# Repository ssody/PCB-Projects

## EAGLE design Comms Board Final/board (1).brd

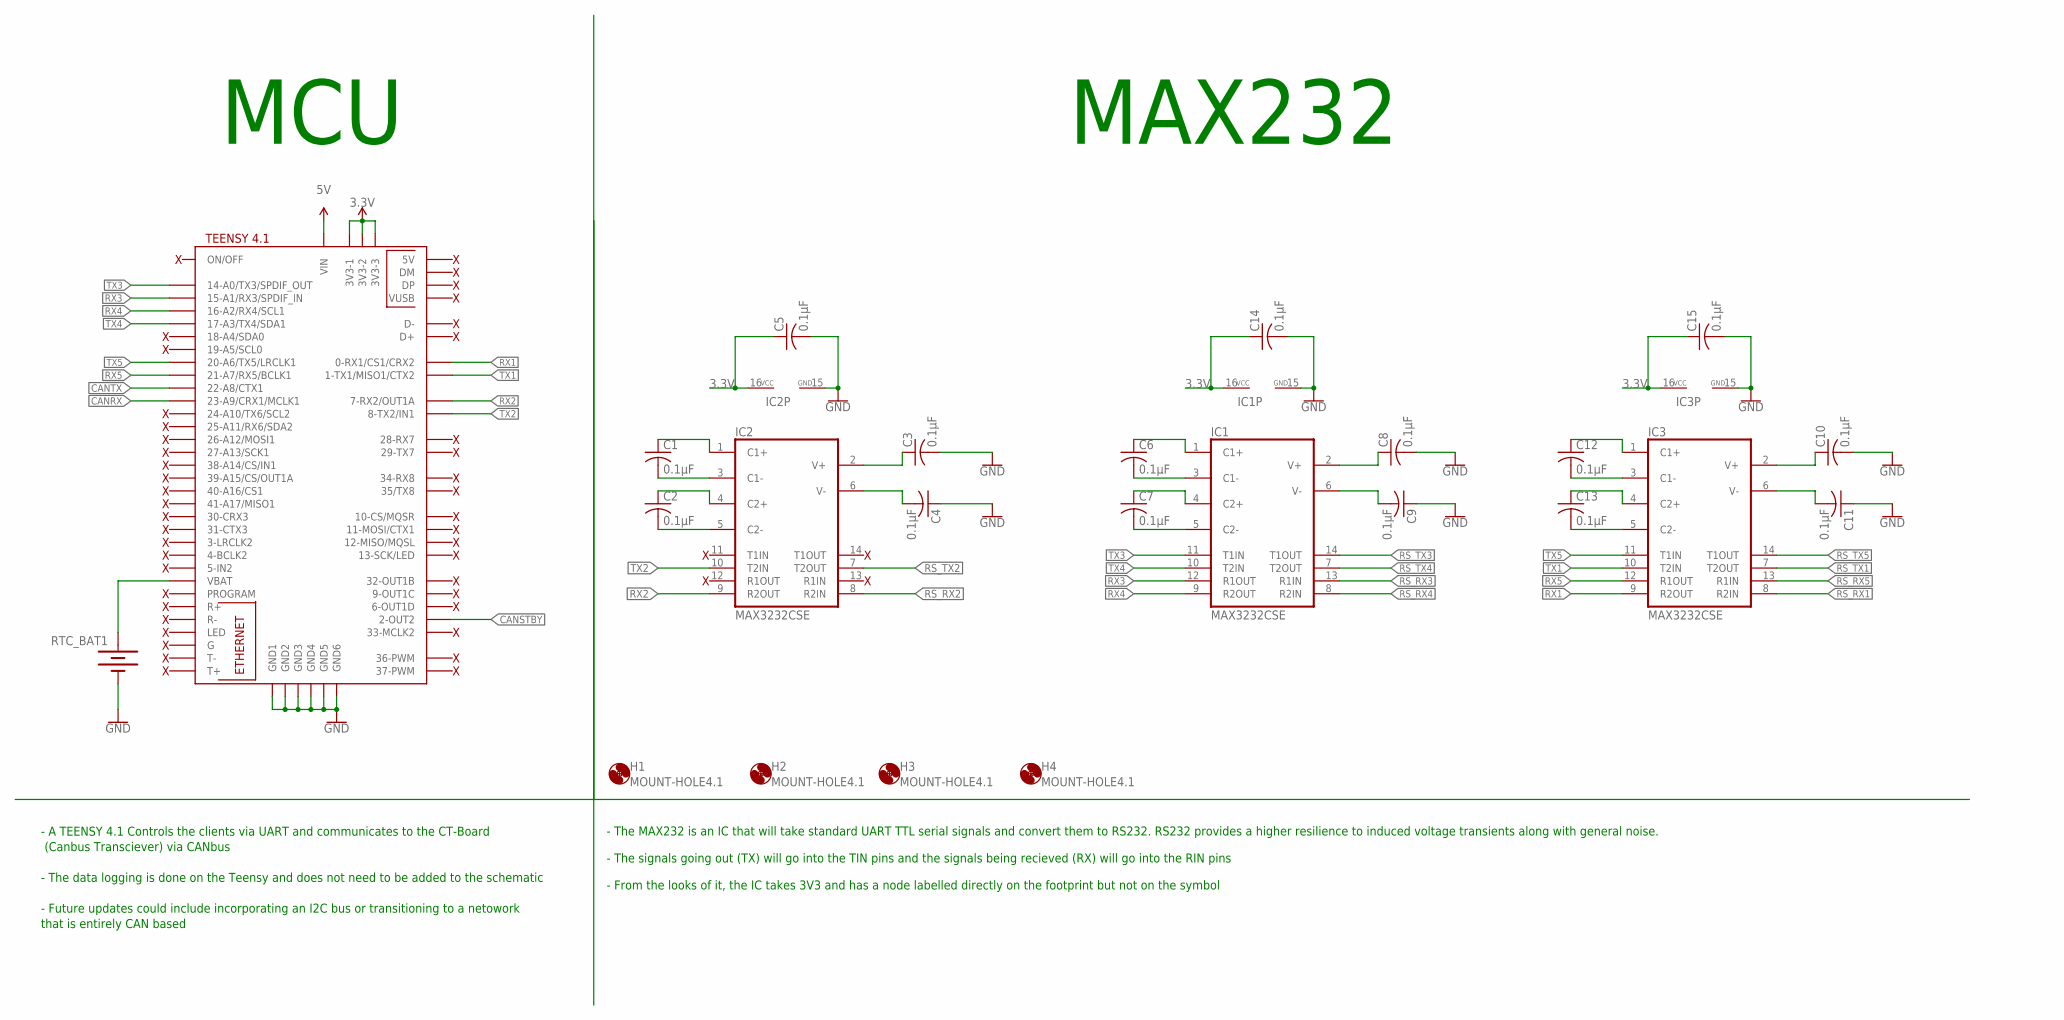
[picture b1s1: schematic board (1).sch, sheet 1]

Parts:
C1, C2, C3, C4, C5, C6, C7, C8, C9, C10, C11, C12, C13, C14, C15: 0.1µF; C0805
H1, H2, H3, H4: MOUNT-HOLE4.1; 4,1
IC1, IC2, IC3: MAX3232CSE; SO16
RTC_BAT1: BATTERY-20MM_PTH; BATTCOM_20MM_PTH
U$1: TEENSY41

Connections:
3.3V: C5.1, C14.1, C15.1, IC1.16 (VCC), IC2.16 (VCC), IC3.16 (VCC), U$1.3V3-1, U$1.3V3-2, U$1.3V3-3; also elsewhere on the board
CANRX: U$1.23-A9/CRX1/MCLK1; also elsewhere on the board
CANSTBY: U$1.2-OUT2; also elsewhere on the board
CANTX: U$1.22-A8/CTX1; also elsewhere on the board
GND: C3.2, C4.1, C5.2, C8.2, C9.1, C10.2, C11.1, C14.2, C15.2, IC1.15 (GND), IC2.15 (GND), IC3.15 (GND), RTC_BAT1.2 (-), U$1.GND1, U$1.GND2, U$1.GND3, U$1.GND4, U$1.GND5, U$1.GND6; also elsewhere on the board
unnamed: C1.1, IC2.1 (C1+)
unnamed: C1.2, IC2.3 (C1-)
unnamed: C2.1, IC2.4 (C2+)
unnamed: C2.2, IC2.5 (C2-)
unnamed: C3.1, IC2.2 (V+)
unnamed: C4.2, IC2.6 (V-)
unnamed: C6.2, IC1.3 (C1-)
unnamed: C7.2, IC1.5 (C2-)
unnamed: C6.1, IC1.1 (C1+)
unnamed: C7.1, IC1.4 (C2+)
unnamed: C8.1, IC1.2 (V+)
unnamed: C9.2, IC1.6 (V-)
unnamed: C10.1, IC3.2 (V+)
unnamed: C11.2, IC3.6 (V-)
unnamed: C12.2, IC3.3 (C1-)
unnamed: C13.2, IC3.5 (C2-)
unnamed: C12.1, IC3.1 (C1+)
unnamed: C13.1, IC3.4 (C2+)
unnamed: RTC_BAT1.1 (+), U$1.VBAT
RS_RX1: IC3.8 (R2IN); also elsewhere on the board
RS_RX2: IC2.8 (R2IN); also elsewhere on the board
RS_RX3: IC1.13 (R1IN); also elsewhere on the board
RS_RX4: IC1.8 (R2IN); also elsewhere on the board
RS_RX5: IC3.13 (R1IN); also elsewhere on the board
RS_TX1: IC3.7 (T2OUT); also elsewhere on the board
RS_TX2: IC2.7 (T2OUT); also elsewhere on the board
RS_TX3: IC1.14 (T1OUT); also elsewhere on the board
RS_TX4: IC1.7 (T2OUT); also elsewhere on the board
RS_TX5: IC3.14 (T1OUT); also elsewhere on the board
RX1: IC3.9 (R2OUT), U$1.0-RX1/CS1/CRX2; also elsewhere on the board
RX2: IC2.9 (R2OUT), U$1.7-RX2/OUT1A; also elsewhere on the board
RX3: IC1.12 (R1OUT), U$1.15-A1/RX3/SPDIF_IN; also elsewhere on the board
RX4: IC1.9 (R2OUT), U$1.16-A2/RX4/SCL1; also elsewhere on the board
RX5: IC3.12 (R1OUT), U$1.21-A7/RX5/BCLK1; also elsewhere on the board
TX1: IC3.10 (T2IN), U$1.1-TX1/MISO1/CTX2; also elsewhere on the board
TX2: IC2.10 (T2IN), U$1.8-TX2/IN1; also elsewhere on the board
TX3: IC1.11 (T1IN), U$1.14-A0/TX3/SPDIF_OUT; also elsewhere on the board
TX4: IC1.10 (T2IN), U$1.17-A3/TX4/SDA1; also elsewhere on the board
TX5: IC3.11 (T1IN), U$1.20-A6/TX5/LRCLK1; also elsewhere on the board

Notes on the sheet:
MCU
MAX232
- A TEENSY 4.1 Controls the clients via UART and communicates to the CT-Board (Canbus Transciever) via CANbus - The data logging is done on the Teensy and does not need to be added to the schematic - Future updates could include incorporating an I2C bus or transitioning to a netowork that is entire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
- The MAX232 is an IC that will take standard UART TTL serial signals and convert them to RS232. RS232 provides a higher resilience to induced voltage transients along with general noise. - The signals going out (TX) will go into the TIN pins and the signals being recieved (RX) will go into the RIN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

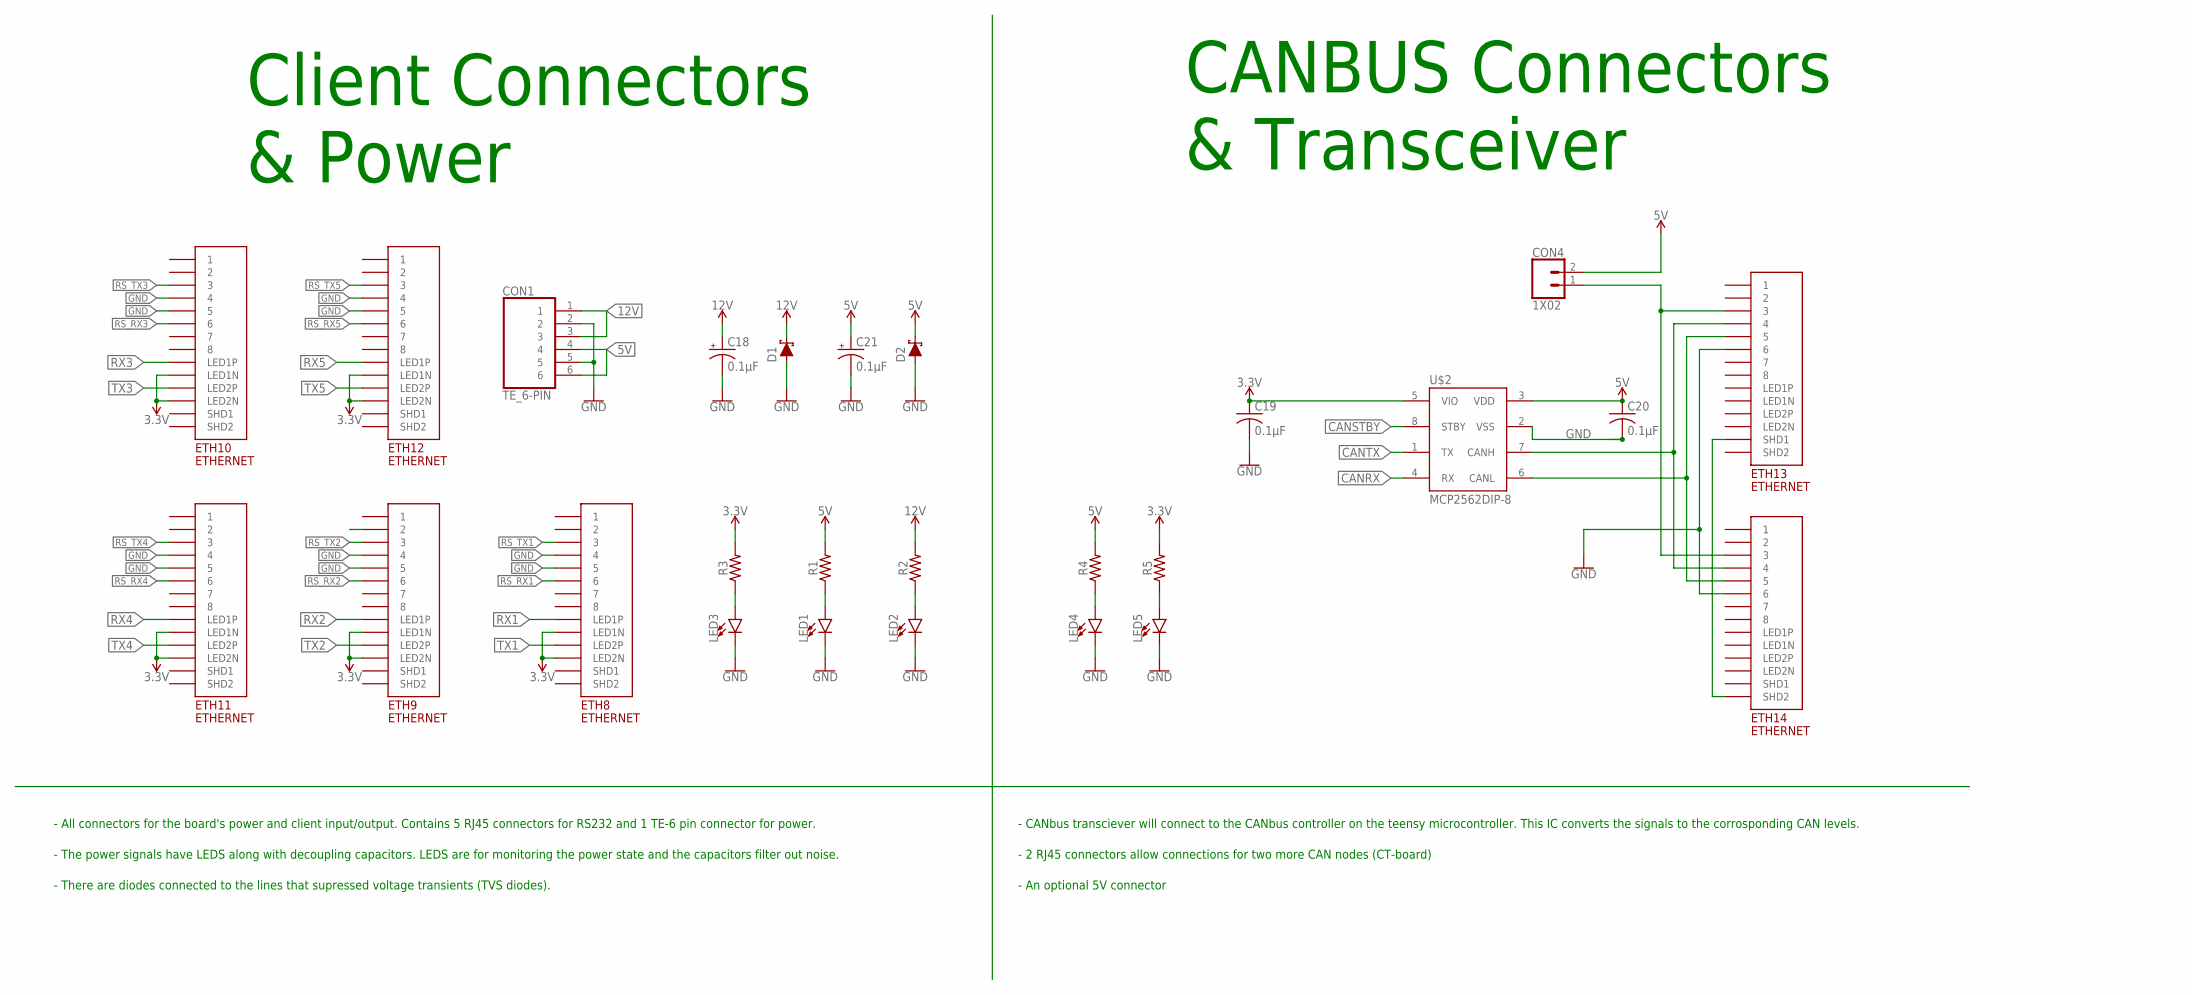
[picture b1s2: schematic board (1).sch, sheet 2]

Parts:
C18, C21: 0.1µF; CAPACITOR_100UF_50V
C19, C20: 0.1µF; C0805
CON1: TE_6-PIN
CON4: 1X02
D1, D2: DIODE_SCHOTTKY_DO-214AA; DO214AA
ETH8, ETH9, ETH10, ETH11, ETH12, ETH13, ETH14: ETHERNET; A122645-ND
LED1, LED2, LED3, LED4, LED5: LED_0805; 0805_LED
R1, R2, R3, R4, R5: RESISTOR_0805; 0805
U$2: MCP2562DIP-8; DIL08

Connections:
3.3V: C19.1, ETH8.P$9 (LED1N), ETH8.P$11 (LED2N), ETH9.P$9 (LED1N), ETH9.P$11 (LED2N), ETH10.P$9 (LED1N), ETH10.P$11 (LED2N), ETH11.P$9 (LED1N), ETH11.P$11 (LED2N), ETH12.P$9 (LED1N), ETH12.P$11 (LED2N), R3.2, R5.2, U$2.5 (VIO); also elsewhere on the board
5V: C20.1, C21.+, CON1.4, CON1.6, CON4.2, D2.C, R1.2, R4.2, U$2.3 (VDD)
12V: C18.+, CON1.1, CON1.3, D1.C, R2.2
CANRX: U$2.4 (RX); also elsewhere on the board
CANSTBY: U$2.8 (STBY); also elsewhere on the board
CANTX: U$2.1 (TX); also elsewhere on the board
GND: C18.-, C19.2, C20.2, C21.-, CON1.2, CON1.5, D1.A, D2.A, ETH8.P$4 (4), ETH8.P$5 (5), ETH9.P$4 (4), ETH9.P$5 (5), ETH10.P$4 (4), ETH10.P$5 (5), ETH11.P$4 (4), ETH11.P$5 (5), ETH12.P$4 (4), ETH12.P$5 (5), ETH13.P$6 (6), ETH14.P$6 (6), LED1.2 (C), LED2.2 (C), LED3.2 (C), LED4.2 (C), LED5.2 (C), U$2.2 (VSS); also elsewhere on the board
unnamed: ETH13.P$4 (4), ETH14.P$4 (4), U$2.7 (CANH)
unnamed: ETH13.P$5 (5), ETH14.P$5 (5), U$2.6 (CANL)
unnamed: CON4.1, ETH13.P$3 (3), ETH14.P$3 (3)
unnamed: ETH13.P$13 (SHD1), ETH14.P$14 (SHD2)
unnamed: LED2.1 (A), R2.1
unnamed: LED1.1 (A), R1.1
unnamed: LED3.1 (A), R3.1
unnamed: LED4.1 (A), R4.1
unnamed: LED5.1 (A), R5.1
RS_RX1: ETH8.P$6 (6); also elsewhere on the board
RS_RX2: ETH9.P$6 (6); also elsewhere on the board
RS_RX3: ETH10.P$6 (6); also elsewhere on the board
RS_RX4: ETH11.P$6 (6); also elsewhere on the board
RS_RX5: ETH12.P$6 (6); also elsewhere on the board
RS_TX1: ETH8.P$3 (3); also elsewhere on the board
RS_TX2: ETH9.P$3 (3); also elsewhere on the board
RS_TX3: ETH10.P$3 (3); also elsewhere on the board
RS_TX4: ETH11.P$3 (3); also elsewhere on the board
RS_TX5: ETH12.P$3 (3); also elsewhere on the board
RX1: ETH8.P$10 (LED1P); also elsewhere on the board
RX2: ETH9.P$10 (LED1P); also elsewhere on the board
RX3: ETH10.P$10 (LED1P); also elsewhere on the board
RX4: ETH11.P$10 (LED1P); also elsewhere on the board
RX5: ETH12.P$10 (LED1P); also elsewhere on the board
TX1: ETH8.P$12 (LED2P); also elsewhere on the board
TX2: ETH9.P$12 (LED2P); also elsewhere on the board
TX3: ETH10.P$12 (LED2P); also elsewhere on the board
TX4: ETH11.P$12 (LED2P); also elsewhere on the board
TX5: ETH12.P$12 (LED2P); also elsewhere on the board

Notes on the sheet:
Client Connectors & Power
CANBUS Connectors & Transceiver
- All connectors for the board's power and client input/output. Contains 5 RJ45 connectors for RS232 and 1 TE-6 pin connector for power. - The power signals have LEDS along with decoupling capacitors. LEDS are for monitoring the power state and the capacitors filter out noise. - There are diodes co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
- CANbus transciever will connect to the CANbus controller on the teensy microcontroller. This IC converts the signals to the corrosponding CAN levels. - 2 RJ45 connectors allow connections for two more CAN nodes (CT-board) - An optional 5V connector

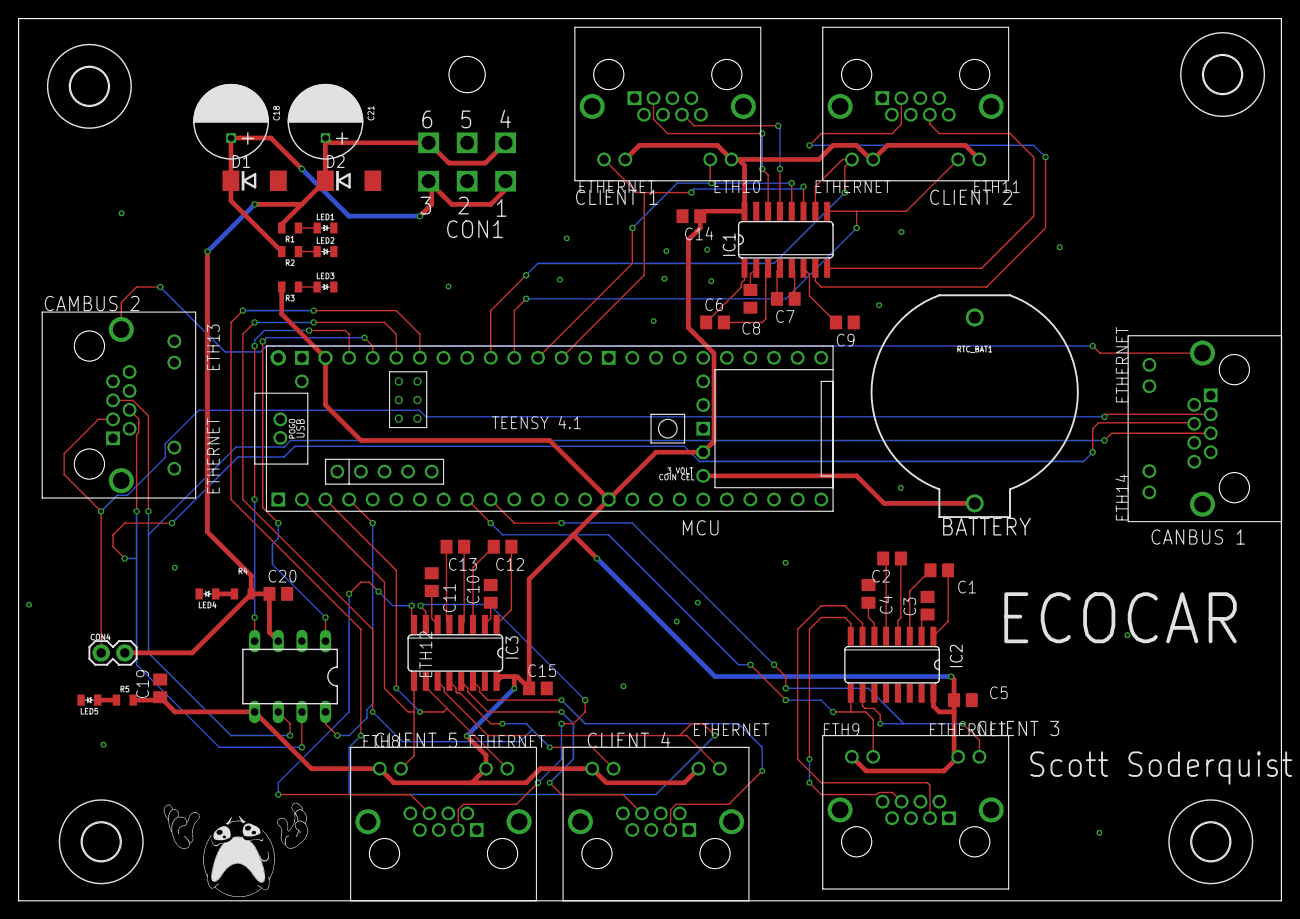
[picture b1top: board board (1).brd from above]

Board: 2 copper layers, 135.9 x 94.9 mm, 50 parts (1 on the bottom side), 55 nets.

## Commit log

2023-02-07 intial commit'
2023-03-04 Create E2-C2 Design 1

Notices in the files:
parts and their libraries:
SparkFun-Batteries: Licensing: Creative Commons ShareAlike 4.0 International - https://creativecommons.org/licenses/by-sa/4.0
